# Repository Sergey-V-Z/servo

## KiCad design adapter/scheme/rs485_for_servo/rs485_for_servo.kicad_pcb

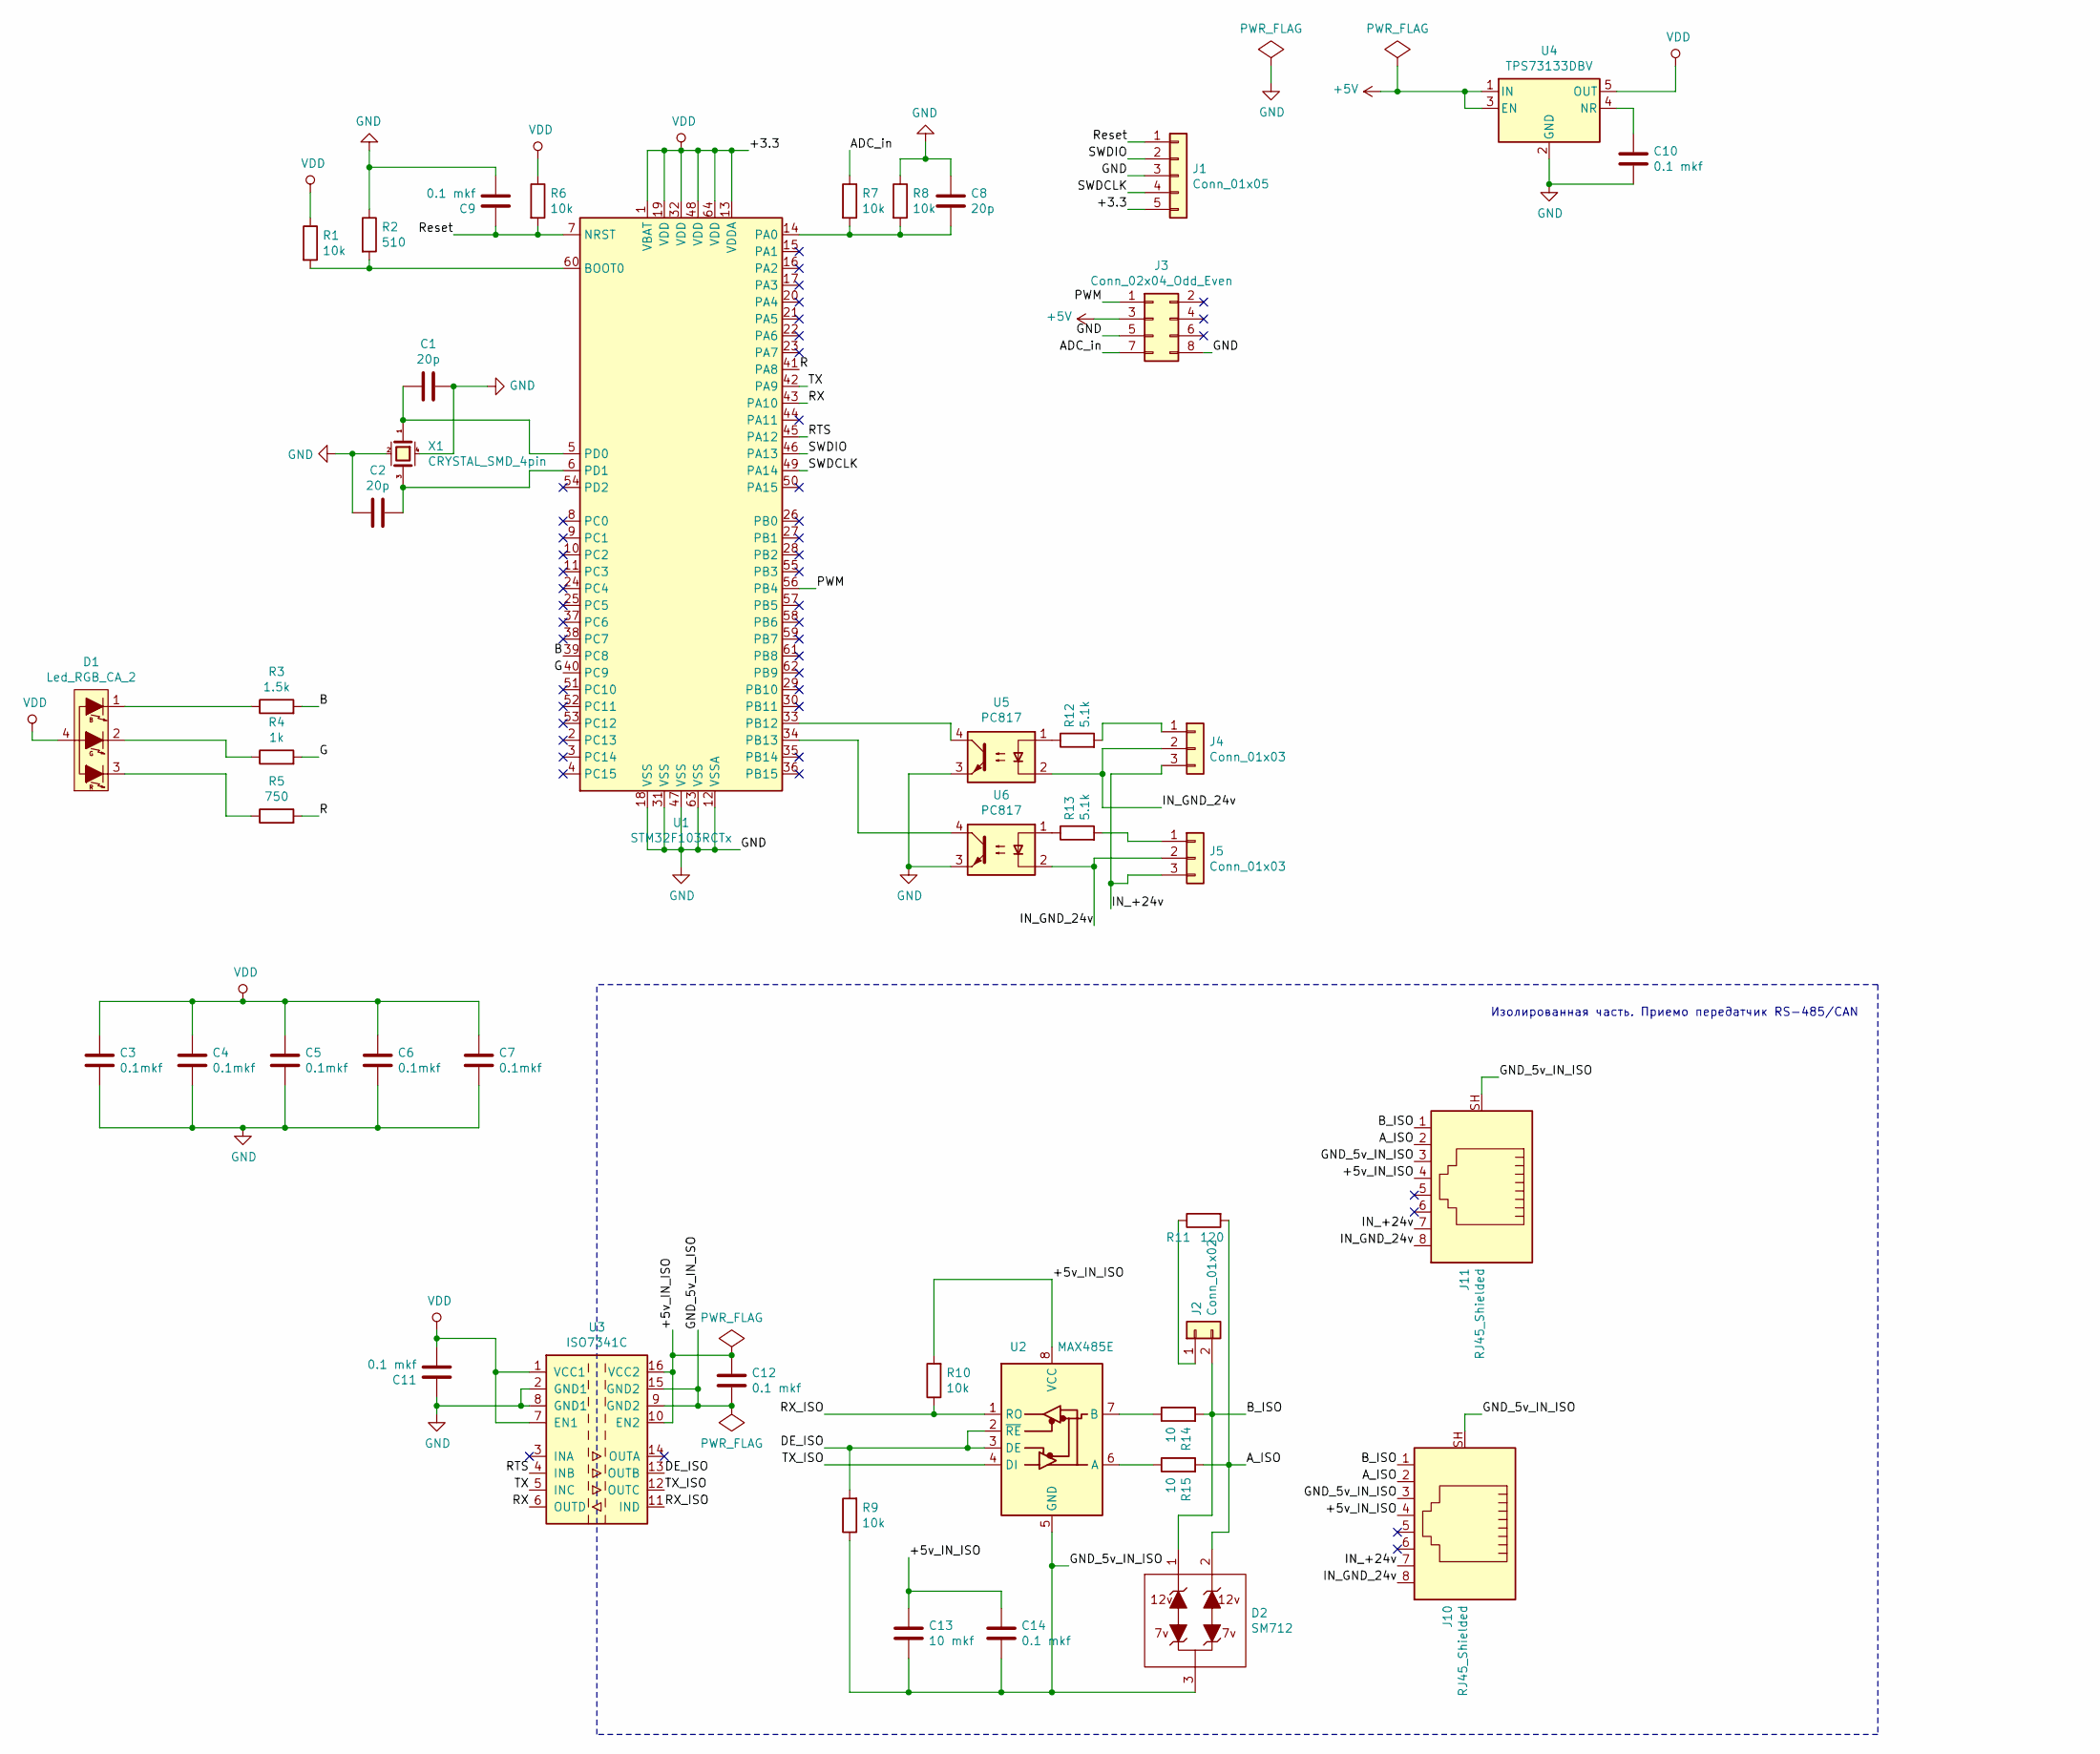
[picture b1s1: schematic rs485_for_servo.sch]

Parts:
C1, C2: 20p; C_0603_1608Metric
C3, C4, C5, C6, C7: 0.1mkf; C_0603_1608Metric
C8: 20p; C_0603_1608Metric_Pad1.05x0.95mm_HandSolder
C9, C10, C11, C12, C14: 0.1 mkf; C_0603_1608Metric_Pad1.05x0.95mm_HandSolder
C13: 10 mkf; C_0805_2012Metric_Pad1.15x1.40mm_HandSolder
D1: Led_RGB_CA_2; LED_Avago_PLCC4_3.2x2.8mm_CW
D2: SM712; SOT-23
J1: Conn_01x05; PinHeader_1x05_P2.54mm_Vertical
J2: Conn_01x02; PinHeader_1x02_P2.54mm_Horizontal
J3: Conn_02x04_Odd_Even; PinSocket_2x04_P2.54mm_Vertical
J4, J5: Conn_01x03; PinHeader_1x03_P2.54mm_Vertical
J10, J11: RJ45_Shielded; RJ45_Ninigi_GE
R1, R6, R7, R8: 10k; R_0805_2012Metric
R2: 510; R_0805_2012Metric
R3: 1.5k; R_0805_2012Metric
R4: 1k; R_0805_2012Metric
R5: 750; R_0805_2012Metric
R9, R10: 10k; R_0805_2012Metric_Pad1.15x1.40mm_HandSolder
R11: 120; R_0805_2012Metric
R12, R13: 5.1k; R_0805_2012Metric
R14, R15: 10; R_0805_2012Metric_Pad1.15x1.40mm_HandSolder
U1: STM32F103RCTx; LQFP-64_10x10mm_P0.5mm
U2: MAX485E; SOIC-8_3.9x4.9mm_P1.27mm
U3: ISO7341C; SOIC-16W_7.5x10.3mm_P1.27mm
U4: TPS73133DBV; SOT-23-5
U5, U6: PC817; SMDIP-4_W9.53mm
X1: CRYSTAL_SMD_4pin; Crystal_SMD_5032-4Pin_5.0x3.2mm

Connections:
+5V: J3.3, U4.1 (IN), U4.3 (EN)
/+5v_IN_ISO: C12.1, C13.1, C14.1, J10.4, J11.4, R10.2, U2.8 (VCC), U3.10 (EN2), U3.16 (VCC2)
/ADC_in: J3.7, R7.1
/A_ISO: D2.2, J10.2, J11.2, R11.2, R15.2
/B: R3.2, U1.39 (PC8)
/B_ISO: D2.1, J2.2, J10.1, J11.1, R14.2
/DE_ISO: R9.2, U2.2 (~RE), U2.3 (DE), U3.13 (OUTB)
/G: R4.2, U1.40 (PC9)
/GND_5v_IN_ISO: C12.2, C13.2, C14.2, D2.3, J10.3, J10.SH, J11.3, J11.SH, R9.1, U2.5 (GND), U3.9 (GND2), U3.15 (GND2)
/IN_+24v: J4.3, J5.3, J10.7, J11.7
/IN_GND_24v: J4.2, J5.2, J10.8, J11.8, U5.2, U6.2
/PWM: J3.1, U1.56 (PB4)
/R: R5.2, U1.41 (PA8)
/RTS: U1.45 (PA12), U3.4 (INB)
/RX: U1.43 (PA10), U3.6 (OUTD)
/RX_ISO: R10.1, U2.1 (RO), U3.11 (IND)
/Reset: C9.1, J1.1, R6.2, U1.7 (NRST)
/SWDCLK: J1.4, U1.49 (PA14)
/SWDIO: J1.2, U1.46 (PA13)
/TX: U1.42 (PA9), U3.5 (INC)
/TX_ISO: U2.4 (DI), U3.12 (OUTC)
GND: C1.1, C2.2, C3.1, C4.1, C5.1, C6.1, C7.1, C8.2, C9.2, C10.2, C11.1, J1.3, J3.5, J3.8, R2.1, R8.1, U1.12 (VSSA), U1.18 (VSS), U1.31 (VSS), U1.47 (VSS), U1.63 (VSS), U3.2 (GND1), U3.8 (GND1), U4.2 (GND), U5.3, U6.3, X1.2 (case), X1.4 (case)
unnamed: C1.2, U1.5 (PD0), X1.1
unnamed: C2.1, U1.6 (PD1), X1.3
unnamed: C8.1, R7.2, R8.2, U1.14 (PA0)
unnamed: C10.1, U4.4 (NR)
unnamed: D1.1 (B), R3.1
unnamed: D1.2 (G), R4.1
unnamed: D1.3 (R), R5.1
unnamed: J2.1, R11.1
unnamed: J4.1, R12.2
unnamed: J5.1, R13.2
unnamed: R1.2, R2.2, U1.60 (BOOT0)
unnamed: R12.1, U5.1
unnamed: R13.1, U6.1
unnamed: R14.1, U2.7 (B)
unnamed: R15.1, U2.6 (A)
unnamed: U1.33 (PB12), U5.4
unnamed: U1.34 (PB13), U6.4
VDD: C3.2, C4.2, C5.2, C6.2, C7.2, C11.2, D1.4, J1.5, R1.1, R6.1, U1.1 (VBAT), U1.13 (VDDA), U1.19 (VDD), U1.32 (VDD), U1.48 (VDD), U1.64 (VDD), U3.1 (VCC1), U3.7 (EN1), U4.5 (OUT)

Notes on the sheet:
Изолированная часть. Приемо передатчик RS-485/CAN

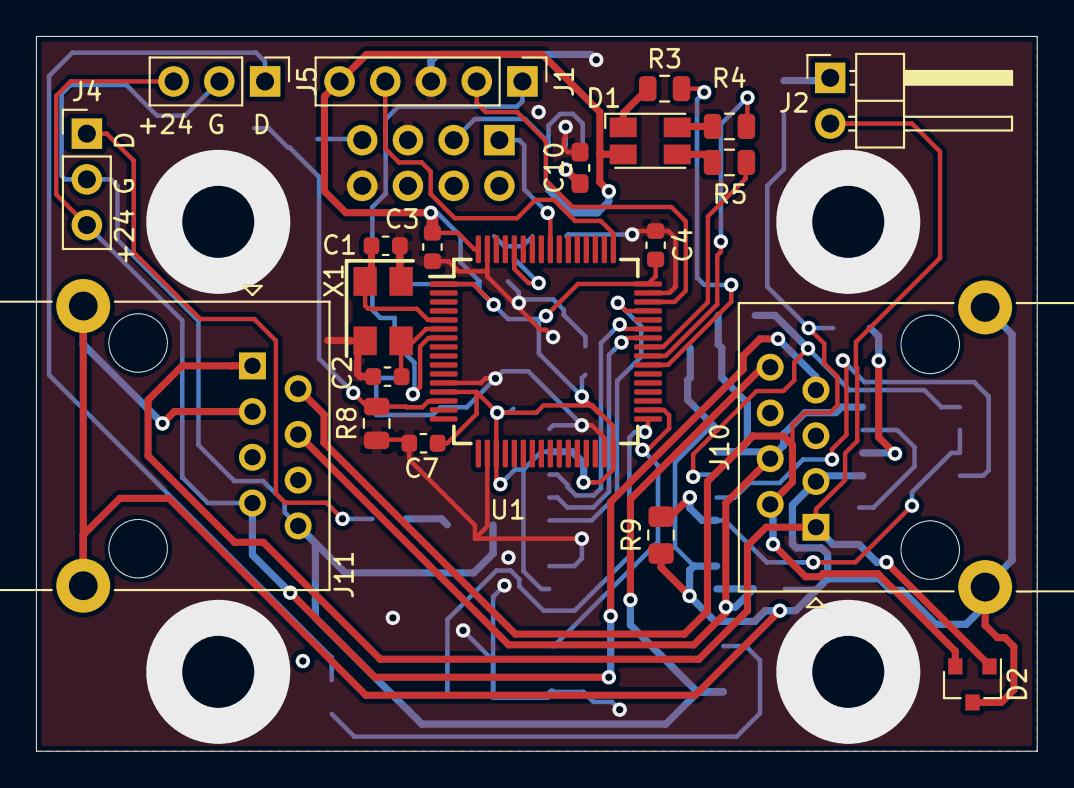
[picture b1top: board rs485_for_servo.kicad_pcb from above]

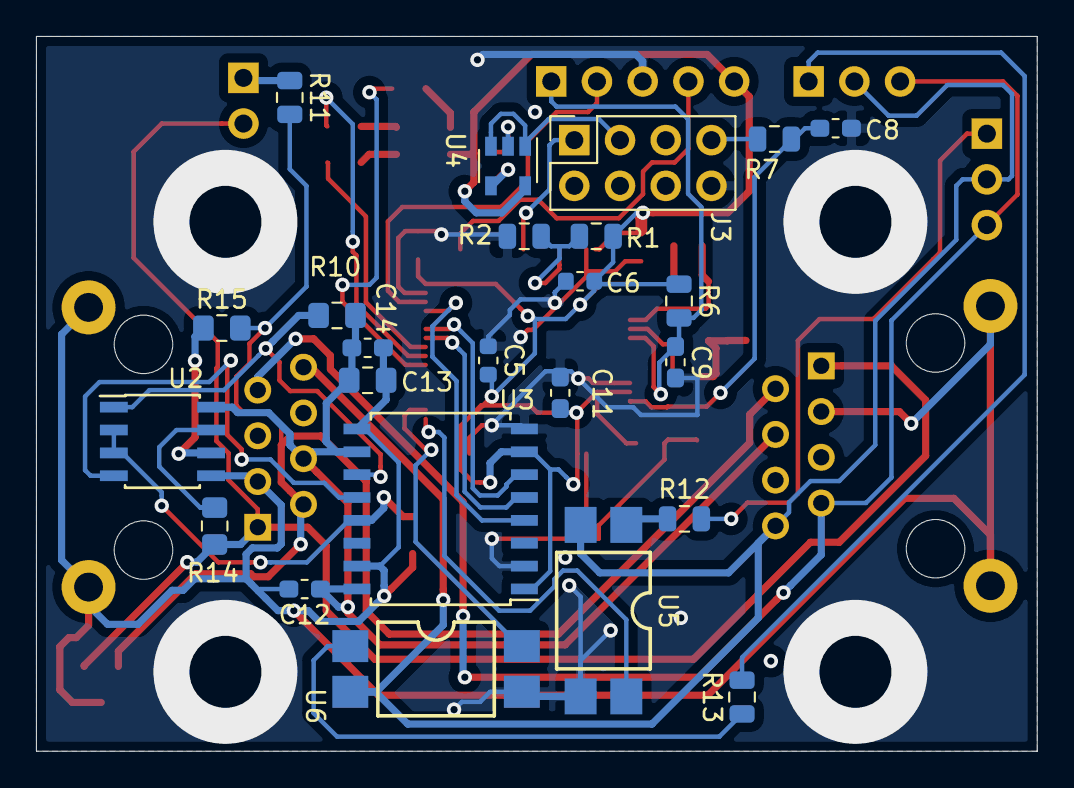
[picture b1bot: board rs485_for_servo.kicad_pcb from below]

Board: 2 copper layers, 55.6 x 39.7 mm, 45 parts (24 on the bottom side), 40 nets.

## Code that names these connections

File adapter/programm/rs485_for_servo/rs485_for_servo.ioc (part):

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Mcu.Name=STM32F103R(C-D-E)Tx
Mcu.Package=LQFP64
Mcu.UserName=STM32F103RCTx
PA0-WKUP.Signal=ADCx_IN0
PA10.Mode=Asynchronous
PA10.Signal=USART1_RX
PA12.GPIOParameters=GPIO_Speed,GPIO_Label
PA12.GPIO_Label=DE
PA12.GPIO_Speed=GPIO_SPEED_FREQ_HIGH
PA12.Signal=GPIO_Output
PA13.Mode=Serial_Wire
PA13.Signal=SYS_JTMS-SWDIO
PA14.Mode=Serial_Wire
PA14.Signal=SYS_JTCK-SWCLK
PA8.GPIOParameters=GPIO_Label,PinState
PA8.GPIO_Label=LED_R
PA8.PinState=GPIO_PIN_SET
PA8.Signal=GPIO_Output
PA9.Mode=Asynchronous
PA9.Signal=USART1_TX
PB12.GPIOParameters=GPIO_PuPd,GPIO_Label
PB12.GPIO_Label=J4
PB12.GPIO_PuPd=GPIO_PULLUP
PB12.Signal=GPIO_Input
PB13.GPIOParameters=GPIO_PuPd,GPIO_Label
PB13.GPIO_Label=J5
PB13.GPIO_PuPd=GPIO_PULLUP
PB13.Signal=GPIO_Input
PB4.GPIOParameters=GPIO_Speed
PB4.GPIO_Speed=GPIO_SPEED_FREQ_HIGH
PB4.Signal=S_TIM3_CH1
PC8.GPIOParameters=GPIO_Label,PinState
PC8.GPIO_Label=LED_B
PC8.PinState=GPIO_PIN_SET
PC8.Signal=GPIO_Output
PC9.GPIOParameters=GPIO_Label,PinState
PC9.GPIO_Label=LED_G
PC9.PinState=GPIO_PIN_SET
PC9.Signal=GPIO_Output
PD0-OSC_IN.Mode=HSE-External-Oscillator
PD0-OSC_IN.Signal=RCC_OSC_IN
PD1-OSC_OUT.Mode=HSE-External-Oscillator
PD1-OSC_OUT.Signal=RCC_OSC_OUT
RCC.SYSCLKFreq_VALUE=72000000
RCC.SYSCLKSource=RCC_SYSCLKSOURCE_PLLCLK
board=custom

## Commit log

2020-07-14 Первый
2020-08-03 Исправление замечаний
    Исправлена ошибка при которой после калибровки привод не двигался(Ошибка: запись значений калибровки в одну переменную).
    Изменено поведение контроллера на команду 0х07, теперь при подаче команды 0 или 1 вал становится в определенную позицию а не меняет положение. Начал писать функцию доводчика до датчика.
2020-08-03 Учтены все замечания
    Начало отладки
2020-08-03 Отладка
2020-08-04 Отладка завершена
